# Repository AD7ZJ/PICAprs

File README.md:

# PIC based APRS Tracking Beacon

I started this project as a fun experiment to see if I could generate an AFSK signal with a small PIC and a resistor ladder network.  It worked out well so I made it into a full tracking beacon.  We fly these on high altitude balloons to track and recover the balloon's payload.  Here's a few of the key features:

- Simple and inexpensive to build.  AFSK is generated using a resistor network so no modem chip is needed
- Adjustable audio output allows interfacing with a variety of radios
- Integrated GPS with helical antenna - no cables to break and works in any orientation
- NMEA data from the GPS is stored on a FAT32 formatted micro SD card
- Software is modular and easy to understand

Well, the last one might be open to debate :-)  It runs on a PIC18F2525 with an SD card hooked up to the SPI port.  I put the GPS and GPS antenna on the same PCB but unfortunately that antenna can no longer be bought from sparkfun - Sarantel seems to be out of business. 

An MPLAB-X project is included and works with the latest version (2.26).  I use the Microchip XC8 compiler.  More details can be seen here: http://wiki.ad7zj.net/wiki/index.php/PIC_APRS_Beacon

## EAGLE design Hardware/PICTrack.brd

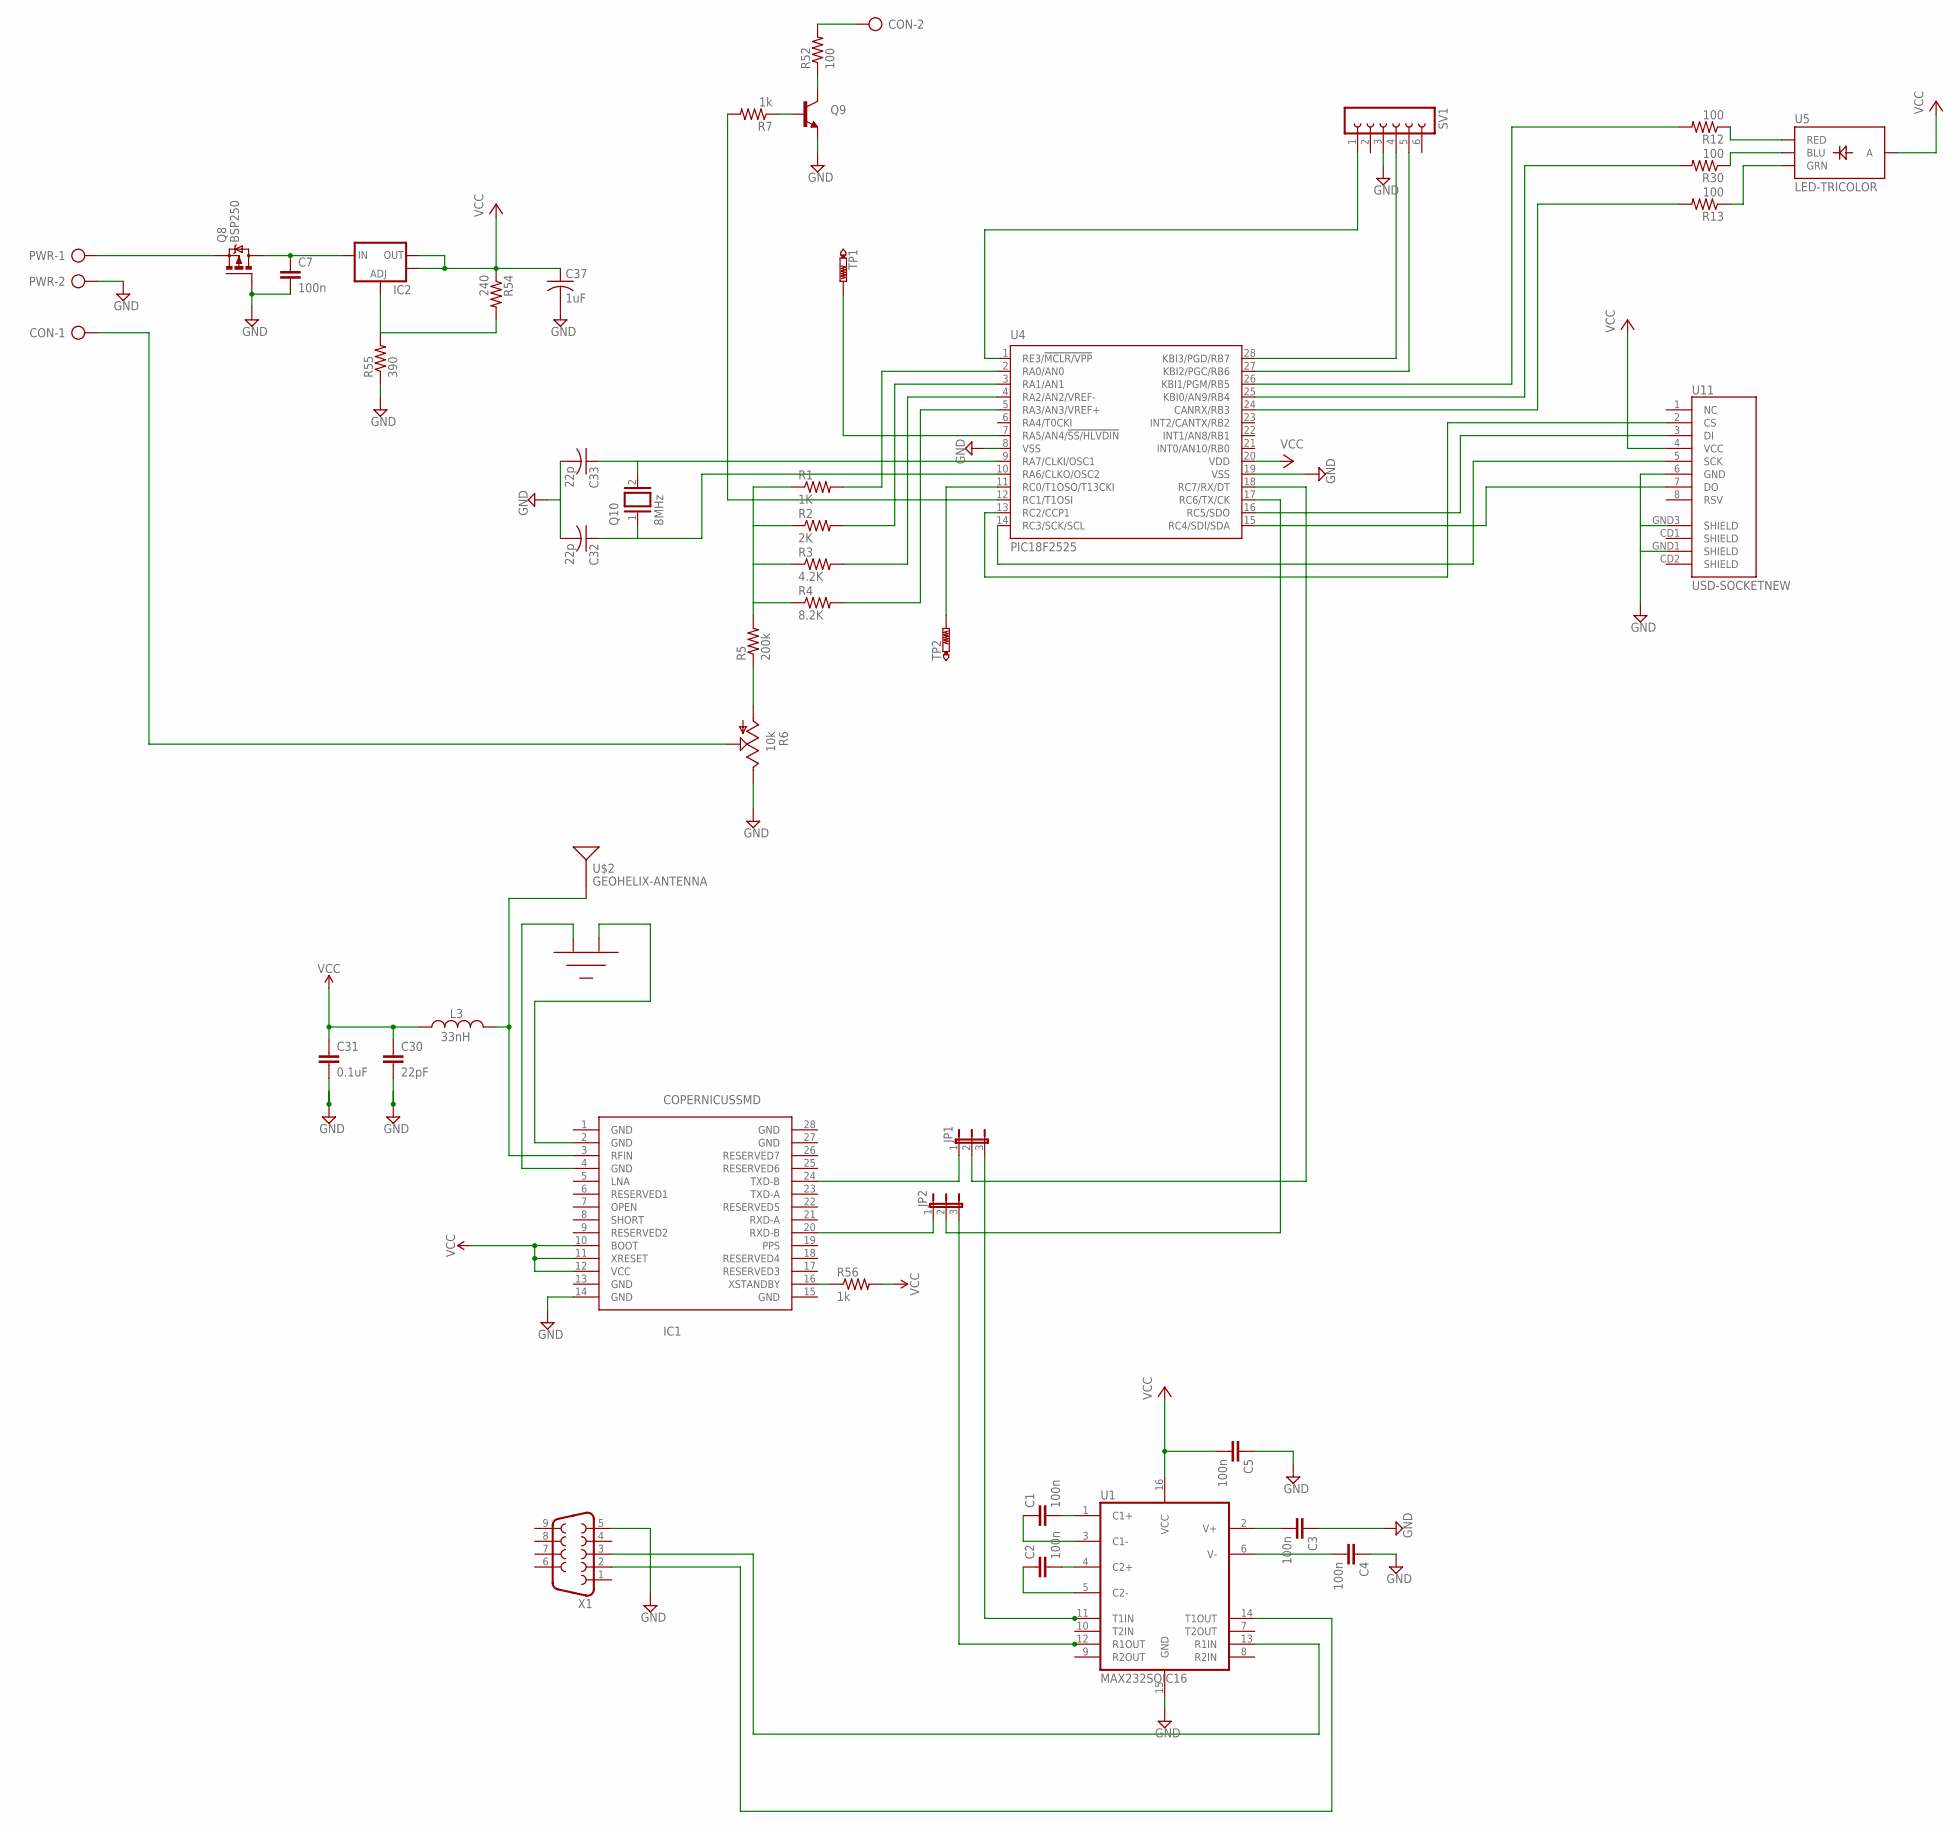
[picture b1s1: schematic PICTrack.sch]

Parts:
C1, C2, C3, C4, C5, C7: 100n; C0402
C30: 22pF; 0402-CAP
C31: 0.1uF; 0402-CAP
C32, C33: 22p; C0603
C37: 1uF; C025-030X050
CON: AK300/2
IC1: COPERNICUSSMD; COPERNICUS
IC2: V_REG_LM1117SOT223; SOT223
JP1, JP2: JP2E; JP2
L3: 33nH; C0402
PWR: AK300/2
Q8: BSP250; SOT223
Q9: TRANSISTOR_NPNSOT23; SOT23
Q10: 8MHz; QS
R1: 1K; 0411V
R2: 2K; 0411V
R3: 4.2K; 0411V
R4: 8.2K; 0411V
R5: 200k; 0411V
R6: 10k; CA6V
R7, R56: 1k; R0603
R12, R13, R30: 100; R0603
R52: 100; 0411V
R54: 240; R0603
R55: 390; R0603
SV1: FE06-1; FE06
TP1, TP2: PTR1PAD1-13; P1-13
U1: MAX232SOIC16; SO016
U4: PIC18F2525; SO28W
U5: LED-TRICOLOR; LED-TRICOLOR-SMD
U11: USD-SOCKETNEW; MICRO-SD-SOCKET-PP
U$2: GEOHELIX-ANTENNA; HELIXANTENNA
X1: DB9FEMALE; DB9

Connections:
GND: C3.1, C4.1, C5.1, C7.2, C30.2, C31.2, C32.2, C33.2, C37.2, IC1.14 (GND), PWR.2, Q8.1 (G), Q9.2 (E), R6.E, R55.1, SV1.3, U1.15 (GND), U4.8 (VSS), U4.19 (VSS), U11.6 (GND), U11.GND1 (SHIELD), U11.GND3 (SHIELD), X1.5
unnamed: R5.1, R6.A
unnamed: R1.2, U4.2 (RA0/AN0)
unnamed: R2.2, U4.3 (RA1/AN1)
unnamed: R3.2, U4.4 (RA2/AN2/VREF-)
unnamed: R4.2, U4.5 (RA3/AN3/VREF+)
unnamed: R1.1, R2.1, R3.1, R4.1, R5.2
unnamed: PWR.1, Q8.3 (S)
unnamed: C1.2, U1.1 (C1+)
unnamed: CON.1, R6.S
unnamed: C1.1, U1.3 (C1-)
unnamed: C2.2, U1.4 (C2+)
unnamed: C2.1, U1.5 (C2-)
unnamed: C3.2, U1.2 (V+)
unnamed: C4.2, U1.6 (V-)
unnamed: SV1.1, U4.1 (RE3/!MCLR/VPP)
unnamed: SV1.4, U4.28 (KBI3/PGD/RB7)
unnamed: IC1.2 (GND), U$2.P$3 (GND1)
unnamed: TP1.TP, U4.7 (RA5/AN4/!SS/HLVDIN)
unnamed: IC1.16 (XSTANDBY), R56.1
unnamed: R12.1, U5.R (RED)
unnamed: R30.1, U5.B (BLU)
unnamed: TP2.TP, U4.11 (RC0/T1OSO/T13CKI)
unnamed: JP1.3, U1.11 (T1IN)
unnamed: IC2.1 (ADJ), R54.2, R55.2
unnamed: Q9.3 (C), R52.1
unnamed: CON.2, R52.2
unnamed: R7.2, U4.12 (RC1/T1OSI)
unnamed: Q9.1 (B), R7.1
unnamed: IC1.4 (GND), U$2.P$1 (GND)
unnamed: U1.13 (R1IN), X1.3
unnamed: U1.14 (T1OUT), X1.2
unnamed: SV1.5, U4.27 (KBI2/PGC/RB6)
unnamed: U4.15 (RC4/SDI/SDA), U11.7 (DO)
unnamed: U4.14 (RC3/SCK/SCL), U11.5 (SCK)
unnamed: U4.16 (RC5/SDO), U11.3 (DI)
unnamed: U4.13 (RC2/CCP1), U11.2 (CS)
unnamed: IC1.24 (TXD-B), JP1.1
unnamed: C32.1, Q10.1, U4.10 (RA6/CLKO/OSC2)
unnamed: C33.1, Q10.2, U4.9 (RA7/CLKI/OSC1)
unnamed: JP2.3, U1.12 (R1OUT)
unnamed: IC1.20 (RXD-B), JP2.1
unnamed: C7.1, IC2.3 (IN), Q8.2 (D)
unnamed: R13.1, U5.G (GRN)
unnamed: R12.2, U4.26 (KBI1/PGM/RB5)
unnamed: R30.2, U4.25 (KBI0/AN9/RB4)
unnamed: R13.2, U4.24 (CANRX/RB3)
RFIN: IC1.3 (RFIN), L3.2, U$2.P$2 (SIGNAL)
RXD: JP2.2, U4.17 (RC6/TX/CK)
TXD: JP1.2, U4.18 (RC7/RX/DT)
VCC: C5.2, C30.1, C31.1, C37.1, IC1.10 (BOOT), IC1.11 (XRESET), IC1.12 (VCC), IC2.2 (OUT), IC2.4 (OUT), L3.1, R54.1, R56.2, U1.16 (VCC), U4.20 (VDD), U5.A, U11.4 (VCC)

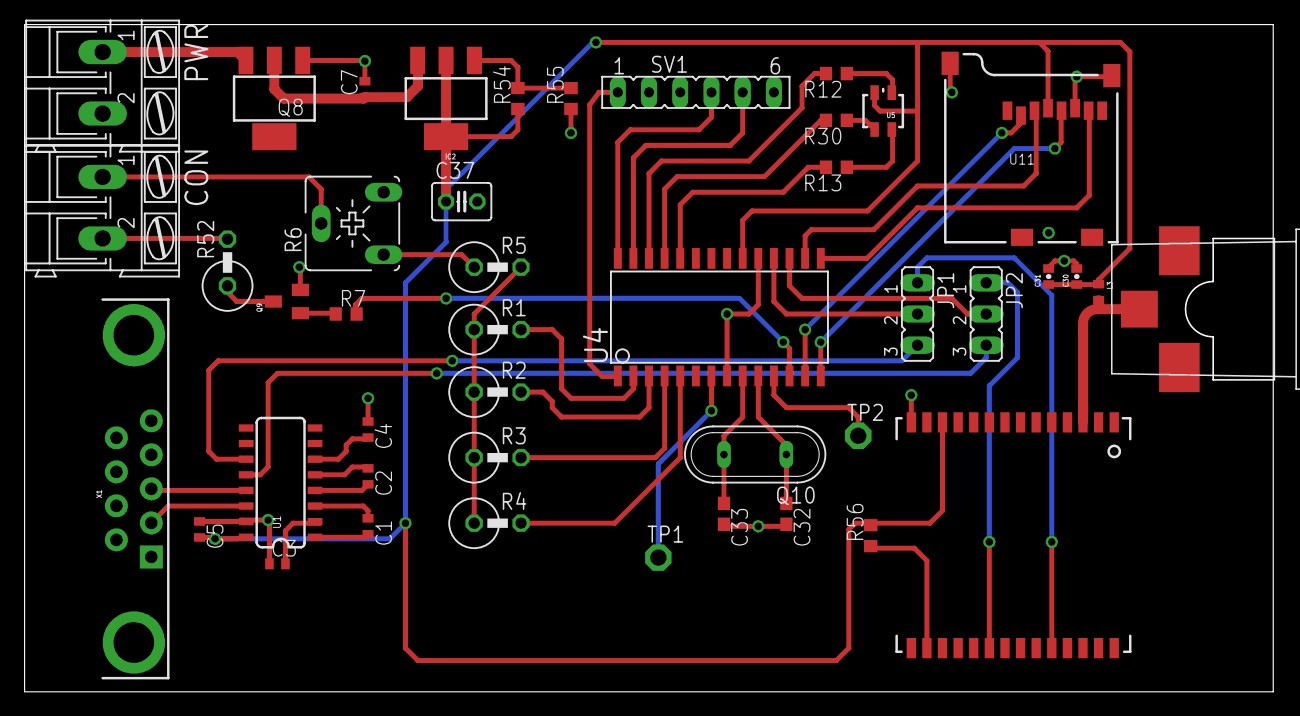
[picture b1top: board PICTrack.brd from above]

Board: 2 copper layers, 101.6 x 54.2 mm, 44 parts (0 on the bottom side), 51 nets.

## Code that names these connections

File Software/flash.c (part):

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
unsigned char  Manufacturer_Id, Device_Type, Device_Id; /* global array to store Manufacturer and Device id information */	

#define SCK RB6
#define SI	RB4
#define	CE	RC6
#define	SO	RC4
#define	SIO2 RC5
#define	SIO3 RC7
				

/************************************************************************/
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
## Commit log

2012-11-06 Initial commit of project
2013-02-09 Fixed build process to compile c files individually
2013-03-10 Added engineering module and refactored some of the other modules. Switched to X IDE
2013-03-27 Fixed the formatting in ax25.c and fixed the issue with the baud rate 'slipping'. This was keeping AGWPE and others from being able to decode the packets.
2013-05-16 Added MPlab X project
2013-10-17 Added GPS module and restructured the layout of a few things
2013-11-01 Restructured a few things and added the mic-e module
2013-11-01 Added schematic and board layout to the project
2013-11-24 Added the LED module. Added logic in the main routine to flash the LED when GPS packets are received.
2013-12-22 Restructured project directories and switched to XC8 compiler
2013-12-22 Added build folder and MPLAB X project files
2013-12-25 Disabled interrupts during packet transmit to avoid corrupting packets if a character is received from the GPS, causing an interrupt. Added logic to the UART RX interrupt handler to clear any overrun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
2013-12-27 Updated doxygen source comments
2013-12-30 Added doxygen comments to main module.
2014-01-01 Added files to support a FAT filesystem. Added test code in main.c to verify the filesystem is working.
2014-01-02 Logging multiple lines is working...
2014-01-02 Re-worked to use chan's full fat filesystem.
2014-01-03 Fixed GPS logging to add a newline to each NMEA string
2014-01-04 Fixed timer 1 configuration so it fires an interrupt every 50ms
2014-03-01 Minimized rounding errors and added a boot message.
2014-07-26 Fixed sin lookup table, tweaked baud rate clock experimentally to be closer to 1200 baud
2014-11-29 Cleaned up unused files and fixed a few comments, updated major revisions in main doxy header
2014-11-29 Added readme file

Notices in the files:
Software/flash.c:
Copyright Silicon Storage Technology, Inc. (SST), 1994-2009
